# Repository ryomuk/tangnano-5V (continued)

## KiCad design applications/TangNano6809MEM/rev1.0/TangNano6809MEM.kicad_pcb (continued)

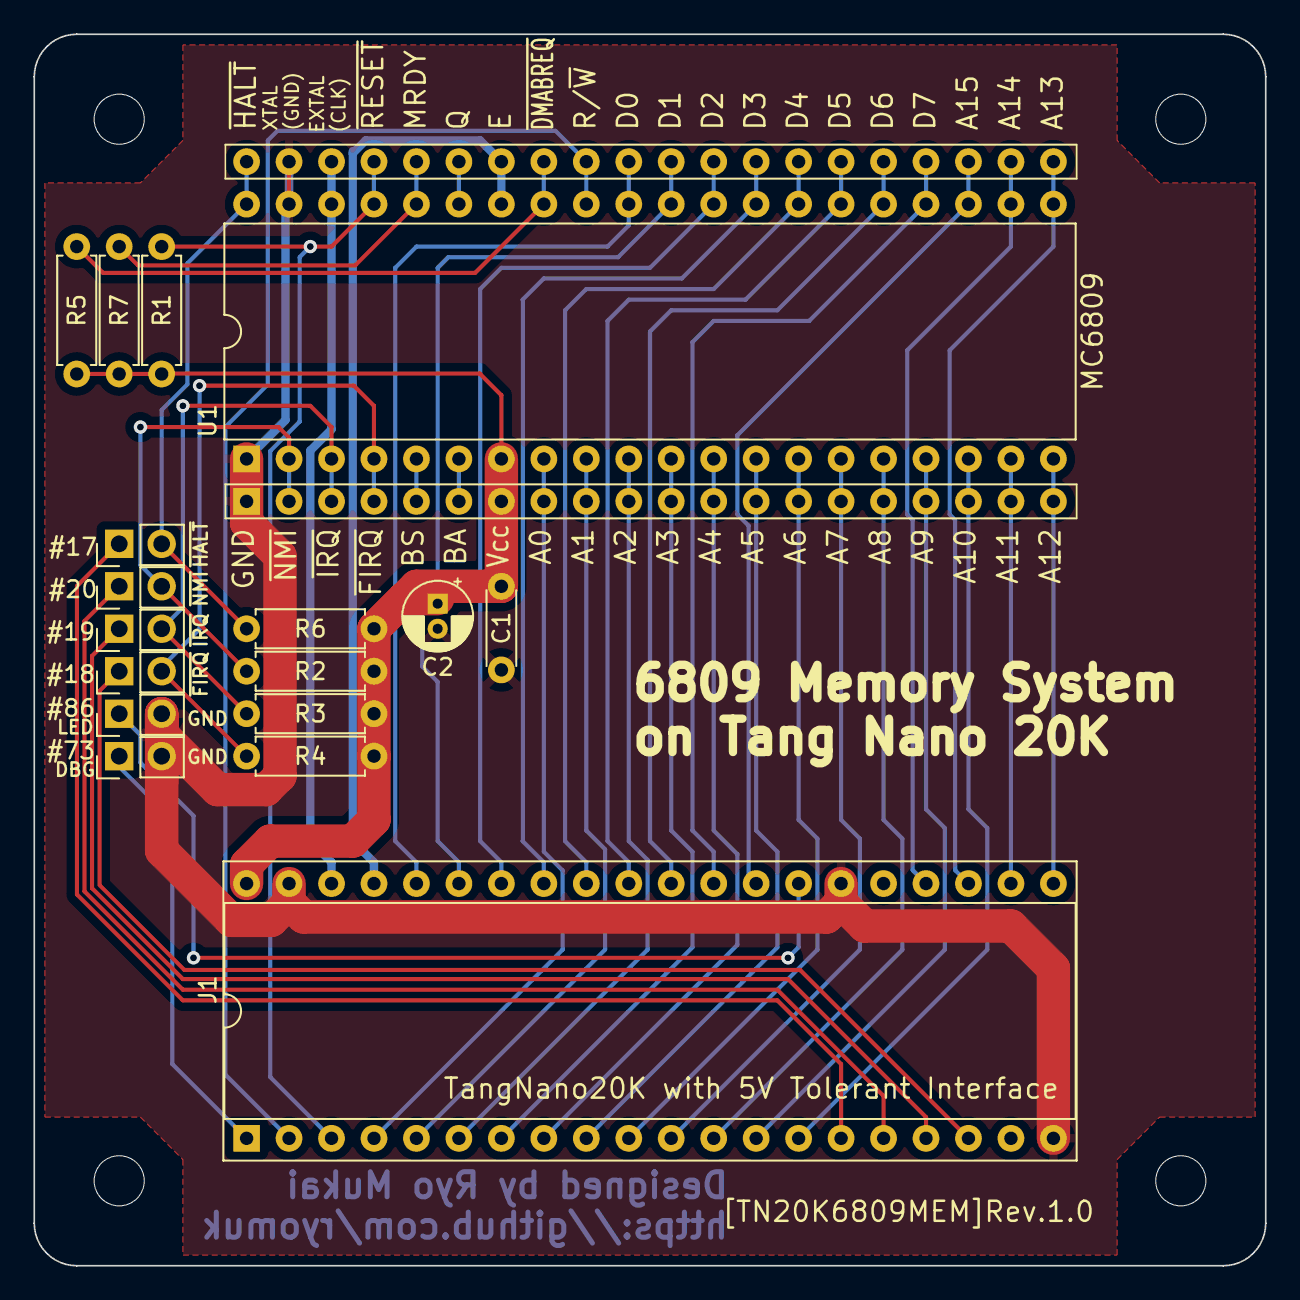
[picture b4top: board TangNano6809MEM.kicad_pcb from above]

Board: 2 copper layers, 73.7 x 73.7 mm, 18 parts (0 on the bottom side), 45 nets.

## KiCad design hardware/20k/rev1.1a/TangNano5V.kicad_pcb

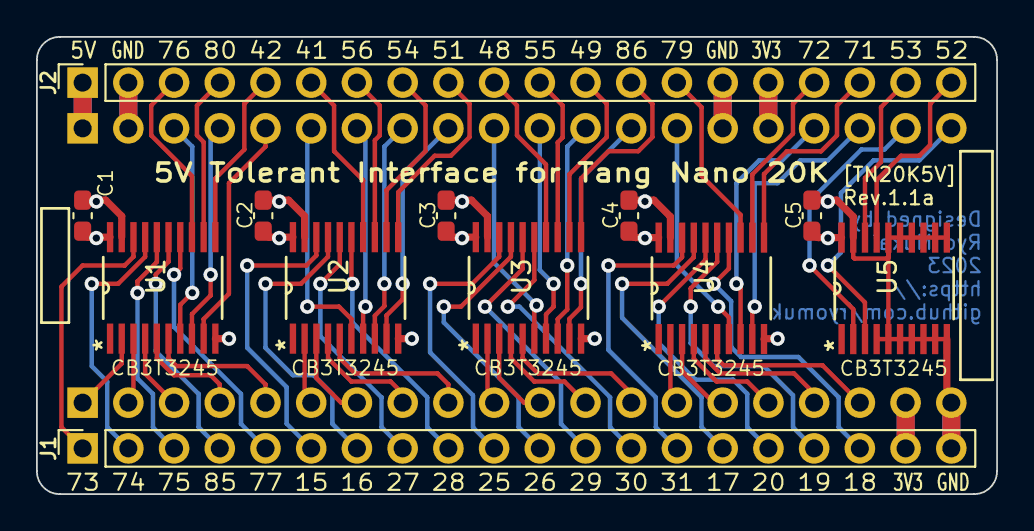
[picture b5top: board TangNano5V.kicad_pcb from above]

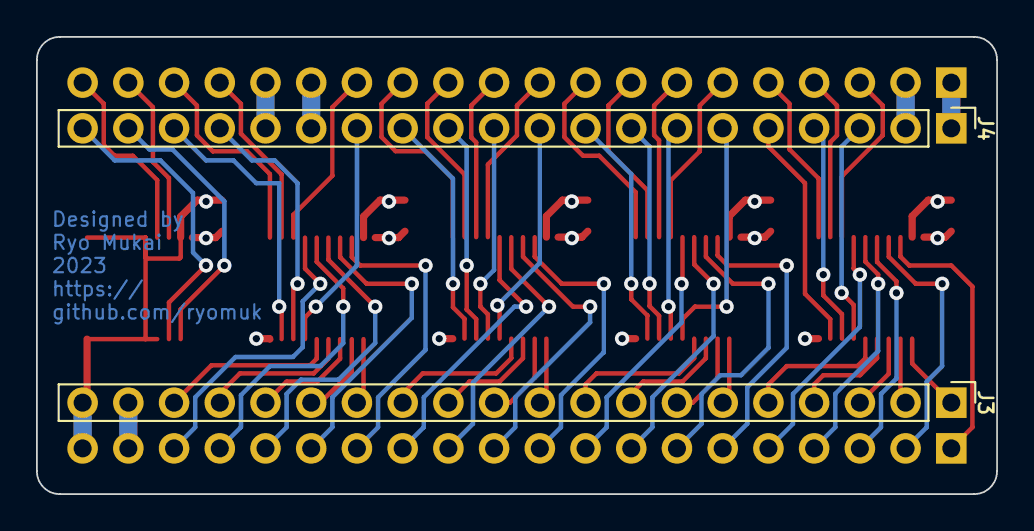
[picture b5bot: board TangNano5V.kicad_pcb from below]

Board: 4 copper layers, 53.3 x 25.4 mm, 14 parts (2 on the bottom side), 71 nets.

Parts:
C1, C2, C3, C4, C5: 0.1uF; C_0603_1608Metric_Pad1.08x0.95mm_HandSolder
J1, J2: TangNano20K; PinSocket_1x20_P2.54mm_Vertical
J3, J4: 5V interface; PinHeader_1x20_P2.54mm_Vertical
U1, U2, U3, U4, U5: CB3T3245; PW20

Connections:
+3.3V: C1.1, C2.1, C3.1, C4.1, C5.1, J1.19, J2.16, J3.19, J4.16, U1.20 (VCC), U2.20 (VCC), U3.20 (VCC), U4.20 (VCC), U5.20 (VCC)
+5V: J2.1, J4.1
GND: C1.2, C2.2, C3.2, C4.2, C5.2, J1.20, J2.2, J2.15, J3.20, J4.2, J4.15, U1.10 (GND), U1.19 (*OE), U2.10 (GND), U2.19 (*OE), U3.10 (GND), U3.19 (*OE), U4.10 (GND), U4.19 (*OE), U5.4 (A3), U5.5 (A4), U5.6 (A5), U5.7 (A6), U5.8 (A7), U5.9 (A8), U5.10 (GND), U5.11 (B8), U5.12 (B7), U5.13 (B6), U5.14 (B5), U5.15 (B4), U5.16 (B3), U5.19 (*OE)
PIN15: J1.6, U2.18 (B1)
PIN15_H: J3.6, U2.2 (A1)
PIN16: J1.7, U2.17 (B2)
PIN16_H: J3.7, U2.3 (A2)
PIN17: J1.15, U4.17 (B2)
PIN17_H: J3.15, U4.3 (A2)
PIN18: J1.18, U4.14 (B5)
PIN18_H: J3.18, U4.6 (A5)
PIN19: J1.17, U4.15 (B4)
PIN19_H: J3.17, U4.5 (A4)
PIN20: J1.16, U4.16 (B3)
PIN20_H: J3.16, U4.4 (A3)
PIN25: J1.10, U3.18 (B1)
PIN25_H: J3.10, U3.2 (A1)
PIN26: J1.11, U3.17 (B2)
PIN26_H: J3.11, U3.3 (A2)
PIN27: J1.8, U2.16 (B3)
PIN27_H: J3.8, U2.4 (A3)
PIN28: J1.9, U2.15 (B4)
PIN28_H: J3.9, U2.5 (A4)
PIN29: J1.12, U3.16 (B3)
PIN29_H: J3.12, U3.4 (A3)
PIN30: J1.13, U3.15 (B4)
PIN30_H: J3.13, U3.5 (A4)
PIN31: J1.14, U4.18 (B1)
PIN31_H: J3.14, U4.2 (A1)
PIN41: J2.6, U2.14 (B5)
PIN41_H: J4.6, U2.6 (A5)
PIN42: J2.5, U1.11 (B8)
PIN42_H: J4.5, U1.9 (A8)
PIN48: J2.10, U3.14 (B5)
PIN48_H: J4.10, U3.6 (A5)
PIN49: J2.12, U3.12 (B7)
PIN49_H: J4.12, U3.8 (A7)
PIN51: J2.9, U2.11 (B8)
PIN51_H: J4.9, U2.9 (A8)
PIN52: J2.20, U5.17 (B2)
PIN52_H: J4.20, U5.3 (A2)
PIN53: J2.19, U5.18 (B1)
PIN53_H: J4.19, U5.2 (A1)
PIN54: J2.8, U2.12 (B7)
PIN54_H: J4.8, U2.8 (A7)
PIN55: J2.11, U3.13 (B6)
PIN55_H: J4.11, U3.7 (A6)
PIN56: J2.7, U2.13 (B6)
PIN56_H: J4.7, U2.7 (A6)
PIN71: J2.18, U4.11 (B8)
PIN71_H: J4.18, U4.9 (A8)
PIN72: J2.17, U4.12 (B7)
PIN72_H: J4.17, U4.8 (A7)
PIN73: J1.1, U1.18 (B1)
PIN73_H: J3.1, U1.2 (A1)
PIN74: J1.2, U1.17 (B2)
PIN74_H: J3.2, U1.3 (A2)
PIN75: J1.3, U1.16 (B3)
PIN75_H: J3.3, U1.4 (A3)
PIN76: J2.3, U1.13 (B6)
PIN76_H: J4.3, U1.7 (A6)
PIN77: J1.5, U1.14 (B5)
PIN77_H: J3.5, U1.6 (A5)
PIN79: J2.14, U4.13 (B6)
PIN79_H: J4.14, U4.7 (A6)
PIN80: J2.4, U1.12 (B7)
PIN80_H: J4.4, U1.8 (A7)
PIN85: J1.4, U1.15 (B4)
PIN85_H: J3.4, U1.5 (A4)
PIN86: J2.13, U3.11 (B8)
PIN86_H: J4.13, U3.9 (A8)

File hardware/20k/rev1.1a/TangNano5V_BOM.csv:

#,Reference,Qty,Value,
1,"C1, C2, C3, C4, C5",5,0.1uF,0603(inch)(1608 (mm))
2,"J1, J2",2,1x20 pin socket for Tang Nano 20K,
3,"J3, J4",2,1x20 pin header for 5V GPIO,
4,"U1, U2, U3, U4, U5",5,SN74CB3T3245PW,

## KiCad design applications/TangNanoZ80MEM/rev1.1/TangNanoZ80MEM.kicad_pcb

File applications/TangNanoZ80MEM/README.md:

# TangNanoZ80MEM
- Z80用のメモリシステムとクロック，UARTです．
- クロックはTTLレベルではなくHでVcc-0.6Vのレベルが必要なので外付けのICで引き上げています．4MHz程度であれば330Ωプルアップ抵抗だけでも動きました．
- Z84C0020，ブレッドボードで20.25MHzで動作しました．
- Z80のVccをTangNano側のVCC(USB給電)と別にしたいこともあるかもしれないので，ピンヘッダで接続するようにしています．
- DBG_TRGとLED_RGBはデバッグ用の信号です．
- 75番ピンはRESET_nに割り当てたのでC51を外さなくても動作します．
- PCB版で27MHz(USB給電，Vcc=4.94V), 33MHz(Z80はTangNanoと別給電, Vcc=6.0V)で動作しました．(2023/7/6)
- uart.vにバグがあったので修正しました．(2024/4/7)
- top.vのデフォルトのクロック周波数を13.5MHzにしました．(2024/4/7)
- uart.vをリファクタリングしました．(2024/4/13)
- top.v: write_memoryのエッジの正負が間違っていたので修正しました．(2024/4/17)
- top.v: RGBLEDで点滅とUARTの状態表示をするようにしました．(2024/4/17)
- top.v: UART_CTRLのrx_data_readyの位置をbit1から0に変更しました．(2024/4/17)
- rom/rom.unimon339.v を同梱しました．ライセンスはファイル参照．(2024/4/17)
- top.v: tx_send関連のタイミングを修正しました．(2024/4/27)

## 関連ブログ
- [Z80をオーバークロックしてみる](https://blog.goo.ne.jp/tk-80/e/6de3708450bac79c2c1cef7728d0c877)
  
ASCIIART.BAS実行結果 (33MHz, Vcc=6.0V)

## 更新履歴
- 2023/06/25: 応用例にTangNanoZ80MEMを追加
- 2023/06/26: TangNanoZ80MEMのピン配置を変更．(rev1.0→rev.1.1)
- 2023/06/28: TangNanoZ80MEMの uart.vを更新．
- 2023/07/06: TangNanoZ80MEMを修正．27MHz(Vcc=5.0V), 33MHz(Vcc=6.0V)で動作．
- 2024/04/17: TangNanoZ80MEM: top.v修正(writeのバグ, RGBLED, UART_CTRL)
- 2024/04/17: TangNanoZ80MEM: rom/rom.unimon339.v 追加
- 2024/04/19: TangNanoZ80MEM: rom/bin2v.pl修正, romファイルの余計な0フィルを削除
- 2024/04/27: TangNanoZ80MEM: UARTの送信タイミング変更

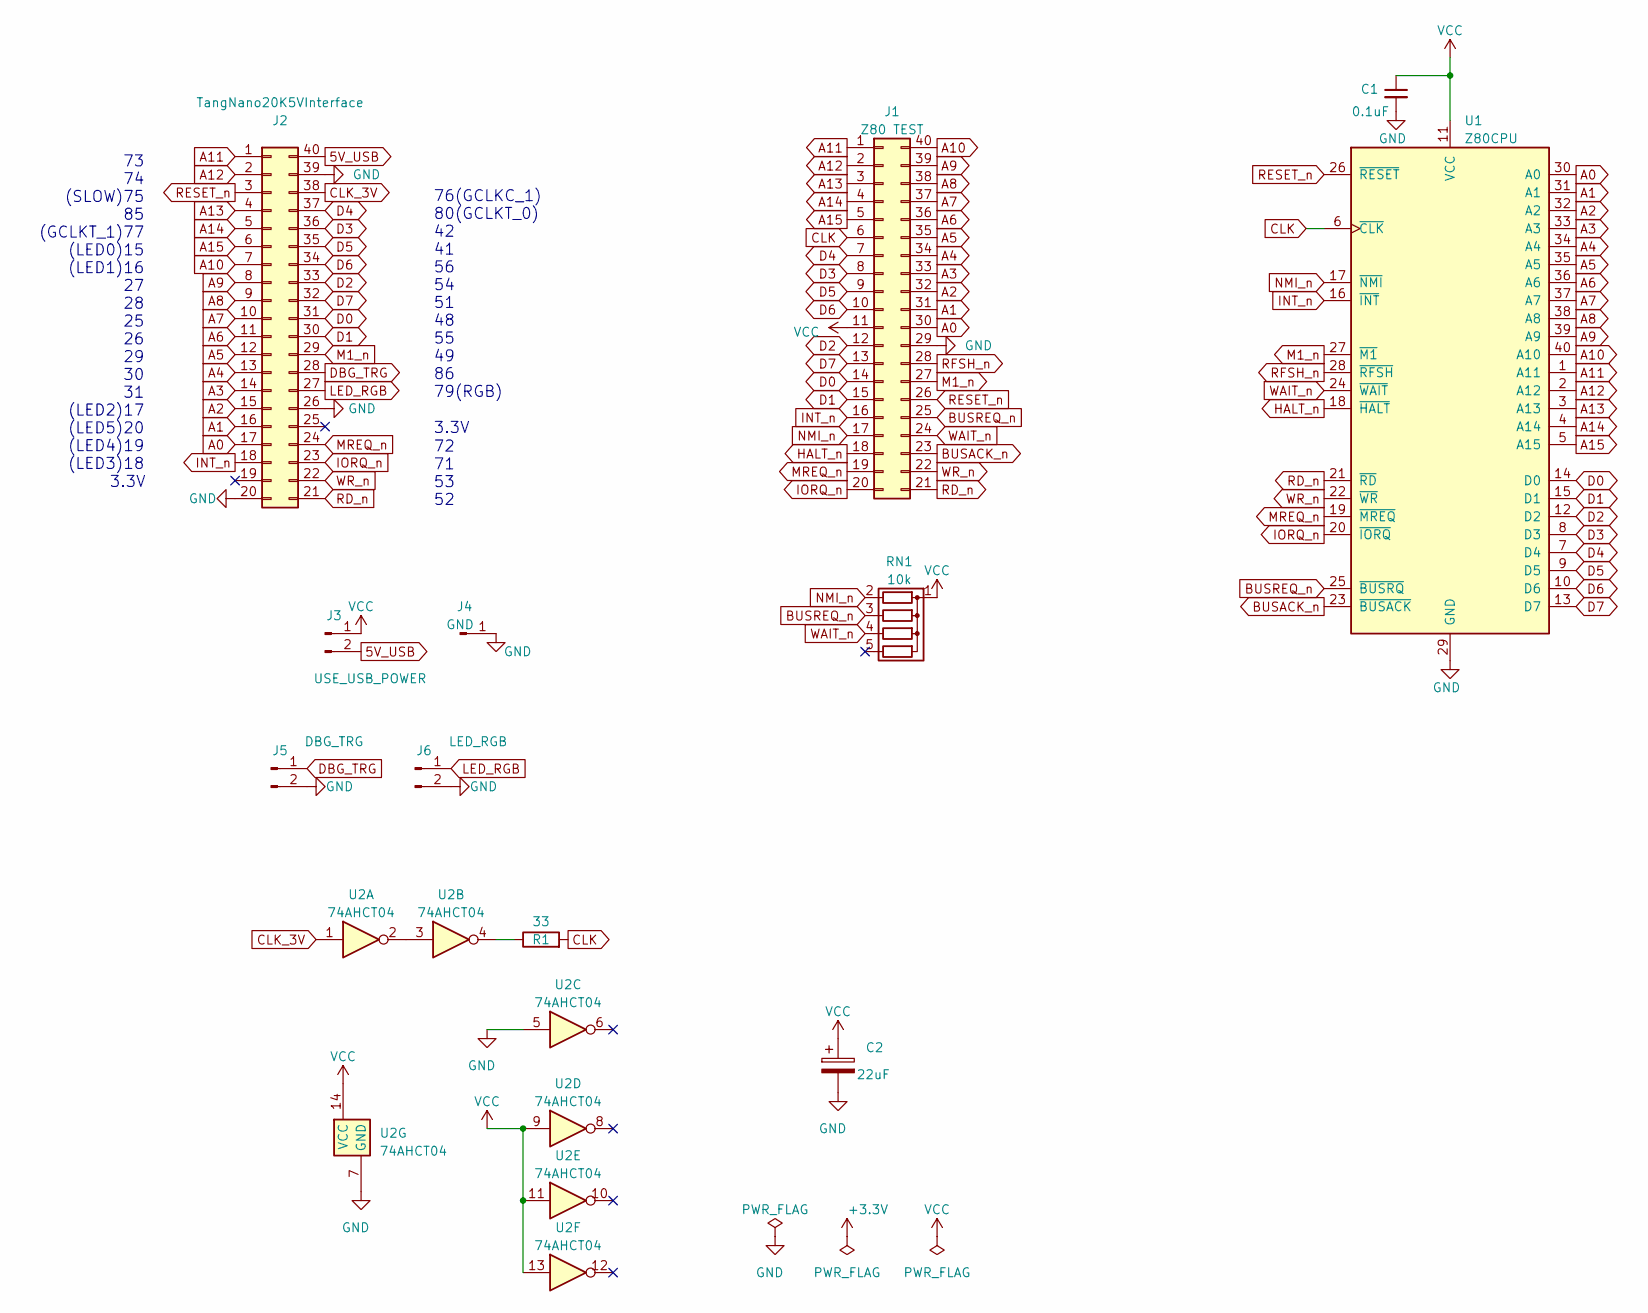
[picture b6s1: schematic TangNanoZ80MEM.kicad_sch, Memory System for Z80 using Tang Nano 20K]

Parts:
C1: 0.1uF; C_Disc_D4.3mm_W1.9mm_P5.00mm
C2: 22uF; CP_Radial_D4.0mm_P1.50mm
J1: Z80 TEST; DIP-40_W20.32mm800mil_Socket
J2: TangNano20K5VInterface; DIP-40_W15.24mm_Socket
J3: USE_USB_POWER; PinHeader_1x02_P2.54mm_Vertical
J4: GND; PinHeader_1x01_P2.54mm_Vertical
J5: DBG_TRG; PinHeader_1x02_P2.54mm_Vertical
J6: LED_RGB; PinHeader_1x02_P2.54mm_Vertical
R1: 33; R_Axial_DIN0207_L6.3mm_D2.5mm_P7.62mm_Horizontal
RN1: 10k; R_Array_SIP5
U1: Z80CPU; DIP-40_W15.24mm_Socket
U2: 74AHCT04; DIP-14_W7.62mm

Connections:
5V_USB: J2.40, J3.2
A0: J1.30, J2.17, U1.30 (A0)
A1: J1.31, J2.16, U1.31 (A1)
A2: J1.32, J2.15, U1.32 (A2)
A3: J1.33, J2.14, U1.33 (A3)
A4: J1.34, J2.13, U1.34 (A4)
A5: J1.35, J2.12, U1.35 (A5)
A6: J1.36, J2.11, U1.36 (A6)
A7: J1.37, J2.10, U1.37 (A7)
A8: J1.38, J2.9, U1.38 (A8)
A9: J1.39, J2.8, U1.39 (A9)
A10: J1.40, J2.7, U1.40 (A10)
A11: J1.1, J2.1, U1.1 (A11)
A12: J1.2, J2.2, U1.2 (A12)
A13: J1.3, J2.4, U1.3 (A13)
A14: J1.4, J2.5, U1.4 (A14)
A15: J1.5, J2.6, U1.5 (A15)
BUSACK_n: J1.23, U1.23 (~BUSACK)
BUSREQ_n: J1.25, RN1.3 (R2), U1.25 (~BUSRQ)
CLK: J1.6, R1.2, U1.6 (~CLK)
CLK_3V: J2.38, U2.1
D0: J1.14, J2.31, U1.14 (D0)
D1: J1.15, J2.30, U1.15 (D1)
D2: J1.12, J2.33, U1.12 (D2)
D3: J1.8, J2.36, U1.8 (D3)
D4: J1.7, J2.37, U1.7 (D4)
D5: J1.9, J2.35, U1.9 (D5)
D6: J1.10, J2.34, U1.10 (D6)
D7: J1.13, J2.32, U1.13 (D7)
DBG_TRG: J2.28, J5.1
GND: C1.2, C2.2, J1.29, J2.20, J2.26, J2.39, J4.1, J5.2, J6.2, U1.29 (GND), U2.5, U2.7 (GND)
HALT_n: J1.18, U1.18 (~HALT)
INT_n: J1.16, J2.18, U1.16 (~INT)
IORQ_n: J1.20, J2.23, U1.20 (~IORQ)
LED_RGB: J2.27, J6.1
M1_n: J1.27, J2.29, U1.27 (~M1)
MREQ_n: J1.19, J2.24, U1.19 (~MREQ)
NMI_n: J1.17, RN1.2 (R1), U1.17 (~NMI)
unnamed: R1.1, U2.4
unnamed: U2.2, U2.3
RD_n: J1.21, J2.21, U1.21 (~RD)
RESET_n: J1.26, J2.3, U1.26 (~RESET)
RFSH_n: J1.28, U1.28 (~RFSH)
VCC: C1.1, C2.1, J1.11, J3.1, RN1.1 (common), U1.11 (VCC), U2.9, U2.11, U2.13, U2.14 (VCC)
WAIT_n: J1.24, RN1.4 (R3), U1.24 (~WAIT)
WR_n: J1.22, J2.22, U1.22 (~WR)

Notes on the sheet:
72 71 53 52
73 74 (SLOW)75 85 (GCLKT_1)77 (LED0)15 (LED1)16 27 28 25 26 29 30 31 (LED2)17 (LED5)20 (LED4)19 (LED3)18
76(GCLKC_1) 80(GCLKT_0) 42 41 56 54 51 48 55 49 86 79(RGB)
3.3V

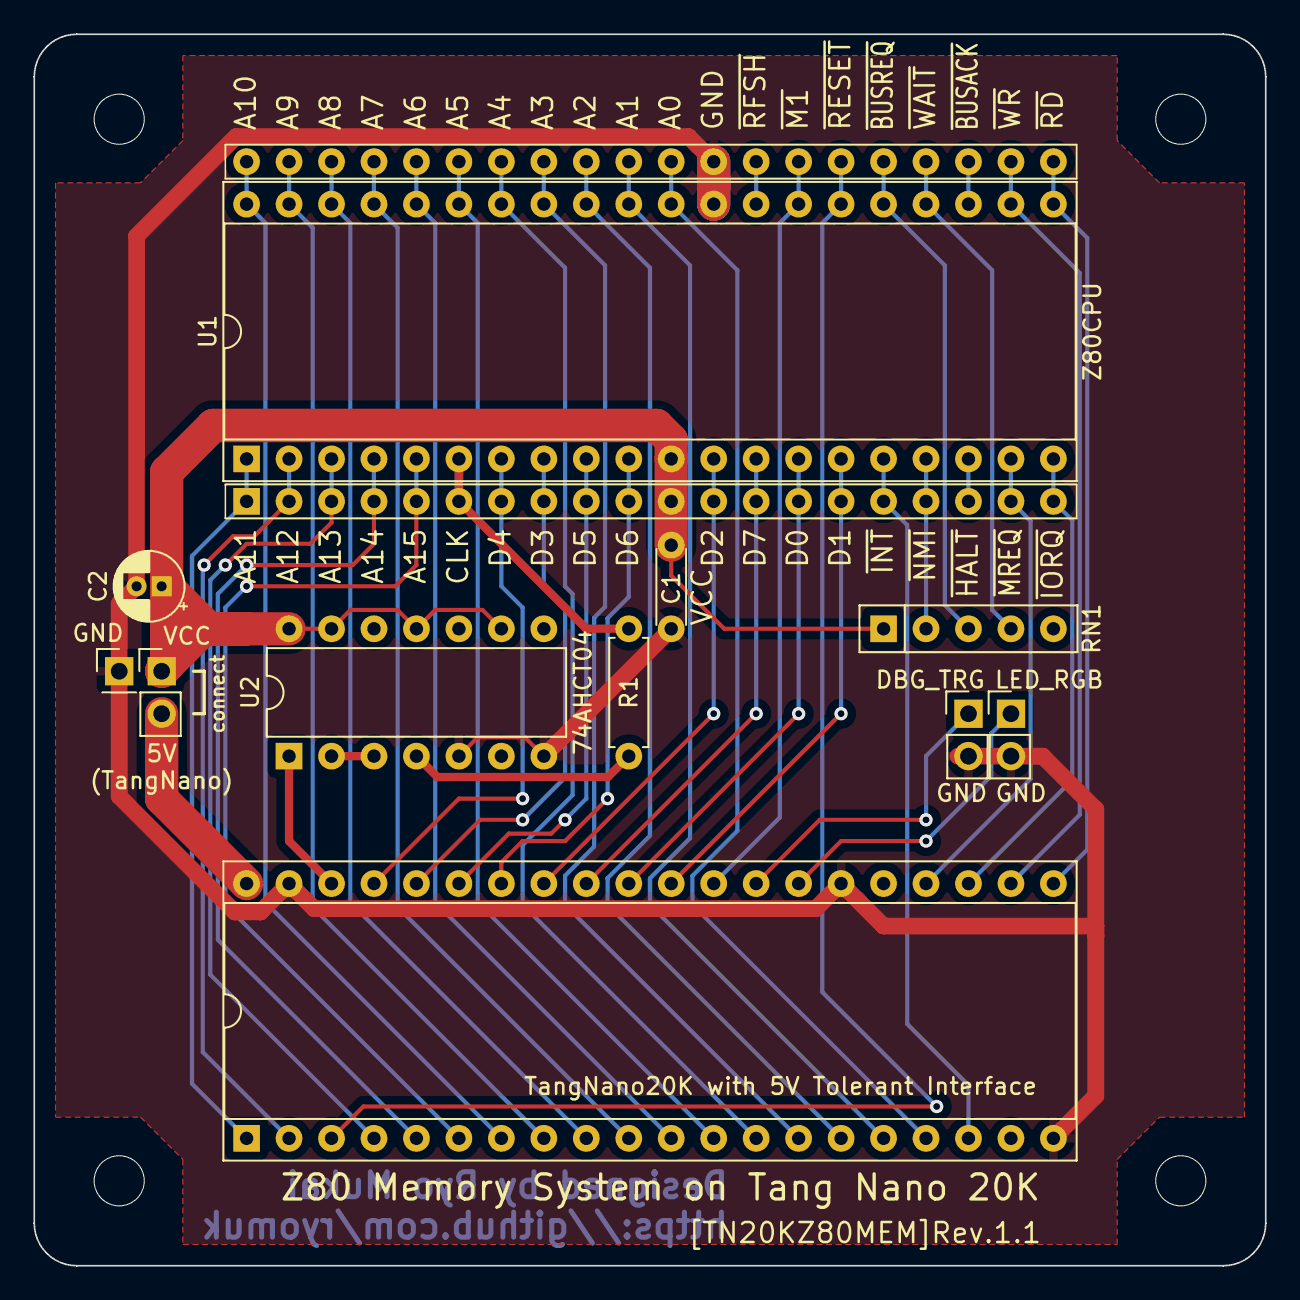
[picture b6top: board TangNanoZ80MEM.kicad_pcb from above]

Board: 2 copper layers, 73.7 x 73.7 mm, 12 parts (0 on the bottom side), 46 nets.

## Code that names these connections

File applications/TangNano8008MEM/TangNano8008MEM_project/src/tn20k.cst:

IO_LOC "sw1"       88; IO_PORT "sw1"     PULL_MODE=NONE IO_TYPE=LVCMOS33;
IO_LOC "sw2"       87; IO_PORT "sw2"     PULL_MODE=NONE IO_TYPE=LVCMOS33;
// sw1 and sw2 are pull downed to GND with 1K on board

IO_LOC "sys_clk"   4; IO_PORT "sys_clk" PULL_MODE=UP IO_TYPE=LVCMOS33;
IO_LOC "usb_rx"   70; IO_PORT "usb_rx" PULL_MODE=UP IO_TYPE=LVCMOS33;
IO_LOC "usb_tx"   69; IO_PORT "usb_tx" PULL_MODE=UP IO_TYPE=LVCMOS33;

// SDCard
//IO_LOC "sd_clk"  83; IO_PORT "sd_clk"  PULL_MODE=NONE IO_TYPE=LVCMOS33; 
//IO_LOC "sd_mosi" 82; IO_PORT "sd_mosi" PULL_MODE=NONE IO_TYPE=LVCMOS33;
//IO_LOC "sd_miso" 84; IO_PORT "sd_miso" PULL_MODE=NONE IO_TYPE=LVCMOS33;
//IO_LOC "sd_cs_n" 81; IO_PORT "sd_cs_n" PULL_MODE=NONE IO_TYPE=LVCMOS33;

IO_LOC "LED_n[5]" 20;
IO_LOC "LED_n[4]" 19;
IO_LOC "LED_n[3]" 18;
IO_LOC "LED_n[2]" 17;
IO_LOC "LED_n[1]" 16;
IO_LOC "LED_n[0]" 15;
IO_PORT "LED_n[5]" PULL_MODE=UP DRIVE=8 IO_TYPE=LVCMOS33;
IO_PORT "LED_n[4]" PULL_MODE=UP DRIVE=8 IO_TYPE=LVCMOS33;
IO_PORT "LED_n[3]" PULL_MODE=UP DRIVE=8 IO_TYPE=LVCMOS33;
IO_PORT "LED_n[2]" PULL_MODE=UP DRIVE=8 IO_TYPE=LVCMOS33;
IO_PORT "LED_n[1]" PULL_MODE=UP DRIVE=8 IO_TYPE=LVCMOS33;
IO_PORT "LED_n[0]" PULL_MODE=UP DRIVE=8 IO_TYPE=LVCMOS33;
//IO_LOC "ws2812" 79;IO_PORT "ws2812" PULL_MODE=UP IO_TYPE=LVCMOS33; // RGB LED

IO_LOC "INTERRUPT" 73; IO_PORT "INTERRUPT" PULL_MODE=UP IO_TYPE=LVCMOS33;
IO_LOC "READY" 74; IO_PORT "READY" PULL_MODE=UP IO_TYPE=LVCMOS33;

// pin75 is pulled down 10k to GND on the board
//IO_LOC "pin75" 75; IO_PORT "pin75" PULL_MODE=NONE IO_TYPE=LVCMOS33;

//IO_LOC "pin85" 85; IO_PORT "pin85" PULL_MODE=UP IO_TYPE=LVCMOS33;
IO_LOC "SYNC" 77; IO_PORT "SYNC" PULL_MODE=UP IO_TYPE=LVCMOS33;

//LED
//IO_LOC "pin15" 15; IO_PORT "pin15" PULL_MODE=UP DRIVE=16 IO_TYPE=LVCMOS33;
//IO_LOC "pin16" 16; IO_PORT "pin16" PULL_MODE=UP DRIVE=16 IO_TYPE=LVCMOS33;

IO_LOC "S[0]" 27; IO_PORT "S[0]" PULL_MODE=UP IO_TYPE=LVCMOS33;
IO_LOC "S[1]" 28; IO_PORT "S[1]" PULL_MODE=UP IO_TYPE=LVCMOS33;
IO_LOC "S[2]" 25; IO_PORT "S[2]" PULL_MODE=UP IO_TYPE=LVCMOS33;
// pin26 is pulled down 5k to GND on the board
//IO_LOC "pin26" 26; IO_PORT "pin26" PULL_MODE=NONE IO_TYPE=LVCMOS33;
//IO_LOC "pin29" 29; IO_PORT "pin29" PULL_MODE=UP IO_TYPE=LVCMOS33;
//IO_LOC "pin30" 30; IO_PORT "pin30" PULL_MODE=UP IO_TYPE=LVCMOS33;
//IO_LOC "pin31" 31; IO_PORT "pin31" PULL_MODE=UP IO_TYPE=LVCMOS33;

//LED
//IO_LOC "pin17" 17; IO_PORT "pin17" PULL_MODE=UP DRIVE=16 IO_TYPE=LVCMOS33;
//IO_LOC "pin20" 20; IO_PORT "pin20" PULL_MODE=UP DRIVE=16 IO_TYPE=LVCMOS33;
//IO_LOC "pin19" 19; IO_PORT "pin19" PULL_MODE=UP DRIVE=16 IO_TYPE=LVCMOS33;
//IO_LOC "pin18" 18; IO_PORT "pin18" PULL_MODE=UP DRIVE=16 IO_TYPE=LVCMOS33;

IO_LOC "CLK1" 76; IO_PORT "CLK1" PULL_MODE=UP DRIVE=16 IO_TYPE=LVCMOS33;
IO_LOC "CLK2" 80; IO_PORT "CLK2" PULL_MODE=UP DRIVE=16 IO_TYPE=LVCMOS33;
IO_LOC "D[7]" 42; IO_PORT "D[7]" PULL_MODE=UP IO_TYPE=LVCMOS33;
IO_LOC "D[6]" 41; IO_PORT "D[6]" PULL_MODE=UP IO_TYPE=LVCMOS33;
IO_LOC "D[5]" 56; IO_PORT "D[5]" PULL_MODE=UP IO_TYPE=LVCMOS33;
IO_LOC "D[4]" 54; IO_PORT "D[4]" PULL_MODE=UP IO_TYPE=LVCMOS33;
IO_LOC "D[3]" 51; IO_PORT "D[3]" PULL_MODE=UP IO_TYPE=LVCMOS33;
IO_LOC "D[2]" 48; IO_PORT "D[2]" PULL_MODE=UP IO_TYPE=LVCMOS33;
IO_LOC "D[1]" 55; IO_PORT "D[1]" PULL_MODE=UP IO_TYPE=LVCMOS33;
IO_LOC "D[0]" 49; IO_PORT "D[0]" PULL_MODE=UP IO_TYPE=LVCMOS33;
//IO_LOC "pin86" 86; IO_PORT "pin86" PULL_MODE=UP IO_TYPE=LVCMOS33;
IO_LOC "LED_RGB"  79; IO_PORT "LED_RGB" PULL_MODE=UP IO_TYPE=LVCMOS33;
IO_LOC "DBG_TRG2" 72; IO_PORT "DBG_TRG2" PULL_MODE=UP IO_TYPE=LVCMOS33;
IO_LOC "DBG_TRG" 71; IO_PORT "DBG_TRG" PULL_MODE=UP IO_TYPE=LVCMOS33;

// pin52 and 53 are pulled up 2.2k to 5V, FET to 3.3V on the board
IO_LOC "GPIO_RX"  53; IO_PORT "GPIO_RX" PULL_MODE=UP IO_TYPE=LVCMOS33;
IO_LOC "GPIO_TX"  52; IO_PORT "GPIO_TX" PULL_MODE=UP IO_TYPE=LVCMOS33;

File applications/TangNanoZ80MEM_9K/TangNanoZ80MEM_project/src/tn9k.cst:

IO_LOC  "led[5]"    16; IO_PORT "led[5]" PULL_MODE=UP DRIVE=8;
IO_LOC  "led[4]"    15; IO_PORT "led[4]" PULL_MODE=UP DRIVE=8;
IO_LOC  "led[3]"    14; IO_PORT "led[3]" PULL_MODE=UP DRIVE=8;
IO_LOC  "led[2]"    13; IO_PORT "led[2]" PULL_MODE=UP DRIVE=8;
IO_LOC  "led[1]"    11; IO_PORT "led[1]" PULL_MODE=UP DRIVE=8;
IO_LOC  "led[0]"    10; IO_PORT "led[0]" PULL_MODE=UP DRIVE=8;
IO_LOC  "sw1_n"      4; IO_PORT "sw1_n" PULL_MODE=UP;
IO_LOC  "sw2_n"      3; IO_PORT "sw2_n" PULL_MODE=UP;
IO_LOC  "sys_clk"   52; IO_PORT "sys_clk" IO_TYPE=LVCMOS33 PULL_MODE=UP;

IO_LOC "uart_tx" 17; IO_PORT "uart_tx" IO_TYPE=LVCMOS33 PULL_MODE=UP;
IO_LOC "uart_rx" 18; IO_PORT "uart_rx" IO_TYPE=LVCMOS33 PULL_MODE=UP;

IO_LOC  "A[10]" 38; IO_PORT "A[10]" IO_TYPE=LVCMOS33 PULL_MODE=UP
IO_LOC  "A[9]" 37; IO_PORT "A[9]" IO_TYPE=LVCMOS33 PULL_MODE=UP
IO_LOC  "A[8]" 36; IO_PORT "A[8]" IO_TYPE=LVCMOS33 PULL_MODE=UP
IO_LOC  "A[7]" 39; IO_PORT "A[7]" IO_TYPE=LVCMOS33 PULL_MODE=UP
IO_LOC  "A[6]" 25; IO_PORT "A[6]" IO_TYPE=LVCMOS33 PULL_MODE=UP
IO_LOC  "A[5]" 26; IO_PORT "A[5]" IO_TYPE=LVCMOS33 PULL_MODE=UP
IO_LOC  "A[4]" 27; IO_PORT "A[4]" IO_TYPE=LVCMOS33 PULL_MODE=UP
IO_LOC  "A[3]" 28; IO_PORT "A[3]" IO_TYPE=LVCMOS33 PULL_MODE=UP
IO_LOC  "A[2]" 29; IO_PORT "A[2]" IO_TYPE=LVCMOS33 PULL_MODE=UP
IO_LOC  "A[1]" 30; IO_PORT "A[1]" IO_TYPE=LVCMOS33 PULL_MODE=UP
IO_LOC  "A[0]" 33; IO_PORT "A[0]" IO_TYPE=LVCMOS33 PULL_MODE=UP
//IO_LOC  "pin34" 34; IO_PORT "pin34" IO_TYPE=LVCMOS33 PULL_MODE=UP
//IO_LOC  "pin40" 40; IO_PORT "pin40" IO_TYPE=LVCMOS33 PULL_MODE=UP
//IO_LOC  "pin35" 35; IO_PORT "pin35" IO_TYPE=LVCMOS33 PULL_MODE=UP
//IO_LOC  "pin41" 41; IO_PORT "pin41" IO_TYPE=LVCMOS33 PULL_MODE=UP
//IO_LOC  "pin42" 42; IO_PORT "pin42" IO_TYPE=LVCMOS33 PULL_MODE=UP
//IO_LOC  "pin51" 51; IO_PORT "pin51" IO_TYPE=LVCMOS33 PULL_MODE=UP
//IO_LOC  "pin53" 53; IO_PORT "pin53" IO_TYPE=LVCMOS33 PULL_MODE=UP
//IO_LOC  "pin54" 54; IO_PORT "pin54" IO_TYPE=LVCMOS33 PULL_MODE=UP
IO_LOC  "D[6]" 34; IO_PORT "D[6]" IO_TYPE=LVCMOS33 PULL_MODE=UP
IO_LOC  "D[2]" 40; IO_PORT "D[2]" IO_TYPE=LVCMOS33 PULL_MODE=UP
IO_LOC  "D[7]" 35; IO_PORT "D[7]" IO_TYPE=LVCMOS33 PULL_MODE=UP
IO_LOC  "D[0]" 41; IO_PORT "D[0]" IO_TYPE=LVCMOS33 PULL_MODE=UP
IO_LOC  "D[1]" 42; IO_PORT "D[1]" IO_TYPE=LVCMOS33 PULL_MODE=UP
IO_LOC  "INT_n" 51; IO_PORT "INT_n" IO_TYPE=LVCMOS33 PULL_MODE=UP
//IO_LOC  "MREQ_n" 55; IO_PORT "MREQ_n" IO_TYPE=LVCMOS33 PULL_MODE=UP
//IO_LOC  "IORQ_n" 56; IO_PORT "IORQ_n" IO_TYPE=LVCMOS33 PULL_MODE=UP
//IO_LOC  "pin55" 55; IO_PORT "pin55" IO_TYPE=LVCMOS33 PULL_MODE=UP
//IO_LOC  "pin56" 56; IO_PORT "pin56" IO_TYPE=LVCMOS33 PULL_MODE=UP
IO_LOC  "DBG_TX[1]" 57; IO_PORT "DBG_TX[1]" IO_TYPE=LVCMOS33 PULL_MODE=UP
IO_LOC  "DBG_TX[0]" 68; IO_PORT "DBG_TX[0]" IO_TYPE=LVCMOS33 PULL_MODE=UP
IO_LOC  "DBG_TRG" 69; IO_PORT "DBG_TRG" IO_TYPE=LVCMOS33 PULL_MODE=UP

IO_LOC  "A[11]" 63; IO_PORT "A[11]" IO_TYPE=LVCMOS33 PULL_MODE=UP
IO_LOC  "A[12]" 86; IO_PORT "A[12]" IO_TYPE=LVCMOS18 PULL_MODE=UP
IO_LOC  "A[13]" 85; IO_PORT "A[13]" IO_TYPE=LVCMOS18 PULL_MODE=UP
IO_LOC  "A[14]" 84; IO_PORT "A[14]" IO_TYPE=LVCMOS18 PULL_MODE=UP
IO_LOC  "A[15]" 83; IO_PORT "A[15]" IO_TYPE=LVCMOS18 PULL_MODE=UP
IO_LOC  "CLK" 82; IO_PORT "CLK" IO_TYPE=LVCMOS18 PULL_MODE=UP
IO_LOC  "D[4]" 81; IO_PORT "D[4]" IO_TYPE=LVCMOS18 PULL_MODE=UP
IO_LOC  "D[3]" 80; IO_PORT "D[3]" IO_TYPE=LVCMOS18 PULL_MODE=UP
IO_LOC  "D[5]" 79; IO_PORT "D[5]" IO_TYPE=LVCMOS18 PULL_MODE=UP
//IO_LOC  "D[6]" 77; IO_PORT "D[6]" IO_TYPE=LVCMOS33 PULL_MODE=UP
//IO_LOC  "D[2]" 76; IO_PORT "D[2]" IO_TYPE=LVCMOS33 PULL_MODE=UP
//IO_LOC  "D[7]" 75; IO_PORT "D[7]" IO_TYPE=LVCMOS33 PULL_MODE=UP
//IO_LOC  "D[0]" 74; IO_PORT "D[0]" IO_TYPE=LVCMOS33 PULL_MODE=UP
//IO_LOC  "D[1]" 73; IO_PORT "D[1]" IO_TYPE=LVCMOS33 PULL_MODE=UP
//IO_LOC  "INT_n" 72; IO_PORT "INT_n" IO_TYPE=LVCMOS33 PULL_MODE=UP
IO_LOC  "MREQ_n" 71; IO_PORT "MREQ_n" IO_TYPE=LVCMOS33 PULL_MODE=UP
IO_LOC  "IORQ_n" 70; IO_PORT "IORQ_n" IO_TYPE=LVCMOS33 PULL_MODE=UP
IO_LOC  "M1_n" 48; IO_PORT "M1_n" IO_TYPE=LVCMOS33 PULL_MODE=UP
IO_LOC  "RESET_n" 49; IO_PORT "RESET_n" IO_TYPE=LVCMOS33 PULL_MODE=UP
IO_LOC  "WR_n" 31; IO_PORT "WR_n" IO_TYPE=LVCMOS33 PULL_MODE=UP
IO_LOC  "RD_n" 32; IO_PORT "RD_n" IO_TYPE=LVCMOS33 PULL_MODE=UP

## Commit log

2023-06-25 Z80 application added
2023-06-25 README updated
2023-06-26 application updated
2023-06-28 uart.v updated
2023-07-06 Z80 application updated
2023-07-11 9K version released
2023-07-15 image updated
2023-07-19 6809MEM added
2023-07-20 photo of rev1.1a added
2023-07-23 TangNano8070MEM added
2023-07-23 pdf of 8070MEM updated
2024-04-07 uart.v bug fixed
2024-04-17 Z80MEM bug fix
2024-04-17 Z80MEM updated
2024-04-19 bin2v.pl updated
2024-04-26 TangNanoZ80MEM updated
2024-06-21 uart.v.20240621 added
2024-07-23 Z80MEM-CPM uploaded
2024-08-05 8008MEM uploaded
2024-08-18 update for VTL-8008
2024-08-28 PCB for 8008 updated
2024-09-08 TangNano8080MEM uploaded
2024-09-13 some image files moved
2025-09-26 impl folders removed
2025-09-26 gitignore added
